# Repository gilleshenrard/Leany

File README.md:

<!--
SPDX-FileCopyrightText: 2025 Gilles Henrard <contact@gilleshenrard.com>

SPDX-License-Identifier: MIT
-->

# Leany - An open-Source Inclinometer

Leany is a fully open-source, production-ready inclinometer based on an ARM Cortex-M3 32-bits microcontroller.
It provides high-precision tilt measurements while adhering to strict embedded software and hardware design standards.

## About the Project
An inclinometer is a tool that measures how much something is tilted, specifically in two directions: pitch and roll.

- Pitch measures the tilt forward or backward. Imagine tilting your head down to look at your feet—that’s pitch.
- Roll measures the tilt side to side. It’s like tilting your head left or right to look over your shoulder—that’s roll.

So, if you're using an inclinometer, it can tell you exactly how much something is tilted forward, backward, or side to side. For example, if you're setting up equipment, you can use the inclinometer to make sure it’s positioned correctly, with no unwanted tilt in either direction. It’s useful in many situations, from construction to vehicles, ensuring that everything is set at the right angle for safety and precision.

Leany is designed for engineers, makers, and professionals who need a reliable, open, and customizable inclinometer. It offers precise tilt measurements and multiple operating modes while maintaining a strong focus on code quality, hardware reliability, and ease of integration.

### Key Features

- **Measurements**: Supports pitch and roll rotation axes with a precision of up to **0.1°**.
- **Hold Function**: Freezes screen updates to keep a measurement visible.
- **Slope Mode**: Measures angles relative to gravity (**absolute measurements**).
- **Angle Mode**: Measures angles relative to a user-defined zero position (**relative measurements**).

## Getting Started

Before contributing, please run the following :
```
git config --local include.path ../.gitconfig
```

To learn more about each part of the project, check the respective directories:

- **[Firmware (`firmware/`)](firmware/)** – Contains the firmware source code and instructions on how to build and flash it.
- **[PCB Design (`pcb/`)](pcb/)** – Contains the schematics and board design, along with instructions on generating production files.
- **[Documentation templates (`templates/`)](templates/)** – Contains example files to illustrate the structure documentation files should have.

## Contributions & Community

Leany is managed with the help of a **[Github Project](https://github.com/users/gilleshenrard/projects/3)**

Leany is fully open-source, and contributions are welcome! If you find a bug, have a suggestion, or want to improve the project, feel free to open an issue or submit a pull request.

Discussions are also encouraged—whether it's feature ideas, improvements, or troubleshooting. Join the community and help make Leany even better!

## License

This project is licensed under the **MIT License**, allowing for flexible use and modification.

---

Feel free to suggest any changes or enhancements to this README! 🚀

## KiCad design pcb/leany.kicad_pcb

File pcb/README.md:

<!--
SPDX-FileCopyrightText: 2026 Gilles Henrard <contact@gilleshenrard.com>

SPDX-License-Identifier: MIT
-->
# Leany Project PCB Documentation

Welcome to the Leany project's PCB documentation. This repository contains all the necessary files and information related to the PCB schematics and layouts for the Leany project.

## Table of Contents

- [Introduction](#introduction)
- [Getting Started](#getting-started)
- [Directory Structure](#directory-structure)
- [Contributing](#contributing)
- [License](#license)

## Introduction

This documentation provides an overview of the PCB schematics and layouts used in the Leany project. It includes detailed information on the design, components, and assembly instructions.

## Introduction

Inspect the project on [KiCanvas](https://kicanvas.org/?repo=https%3A%2F%2Fgithub.com%2Fgilleshenrard%2Fleany%2Ftree%2Fmain%2Fpcb)

## Generate the production files

1. Download KiCad from the [official website](https://kicad.org/).
2. Go to the pcb/ directory
3. Run the generation script located under resources/ :
    - *generate_production_files.bat* on Windows
    - *generate_production_files.sh* on Linux

## PCB fabrication

- Once the production files are generated, head to [JLCPCB](https://cart.jlcpcb.com/quote?orderType=1&stencilLayer=2&stencilWidth=100&stencilLength=100)

- Upload the zipped Gerber file, then, when the website is done processing it, choose the following non-default options :
  - Surface finish : LeadFree HASL
  - Enable PCB Assembly
- Then, click Next until arriving at the Bill Of Materials page.
- Upload the BOM and CPL files and click "Process BOM&CPL".
- Check that no error is shown on the components list page, and click Next.
- On the Components Placement page, move the components which are misplaced, then click Next.
- On the final page, click Save to Cart.

## Directory Structure
```
pcb/
└── resources
    ├── 3d-models
    ├── generate_production_files.sh
    └── generate_production_files.bat
```

### `3d-models`
This directory contains the additional 3D models needed to export the PCB as an STL file.
All the models are organised as [source]/[author]/[file]

### `resources`
Contains additional resources :
- `generate_production_files.sh` : A script to automatically generate and organise production files on Linux, with respect to JLCPCB standards.
- `generate_production_files.sh` : A script to automatically generate and organise production files on Windows, with respect to JLCPCB standards.

## CI/CD workflows
The PCB files are instected by a [Github Action](https://github.com/gilleshenrard/leany/actions/workflows/pcb_production_files.yml) upon push and pull request to run the **Electrical Rules Check** and **Design Rules Check** ensure the production files are easily generated.

## Gallery

## Contributing

Contributions to improve the PCB design and documentation are welcome. If you have any suggestions or improvements, please create a pull request or open an issue on the repository.

## License

The PCB files are licensed under CERN Open Hardware Licence Version 2 - Permissive. See the [CERN-OHL-P-2.0](https://github.com/gilleshenrard/leany/blob/27-fix-pcb-rev02-issues/LICENSES/CERN-OHL-P-2.0.txt) file for more details.

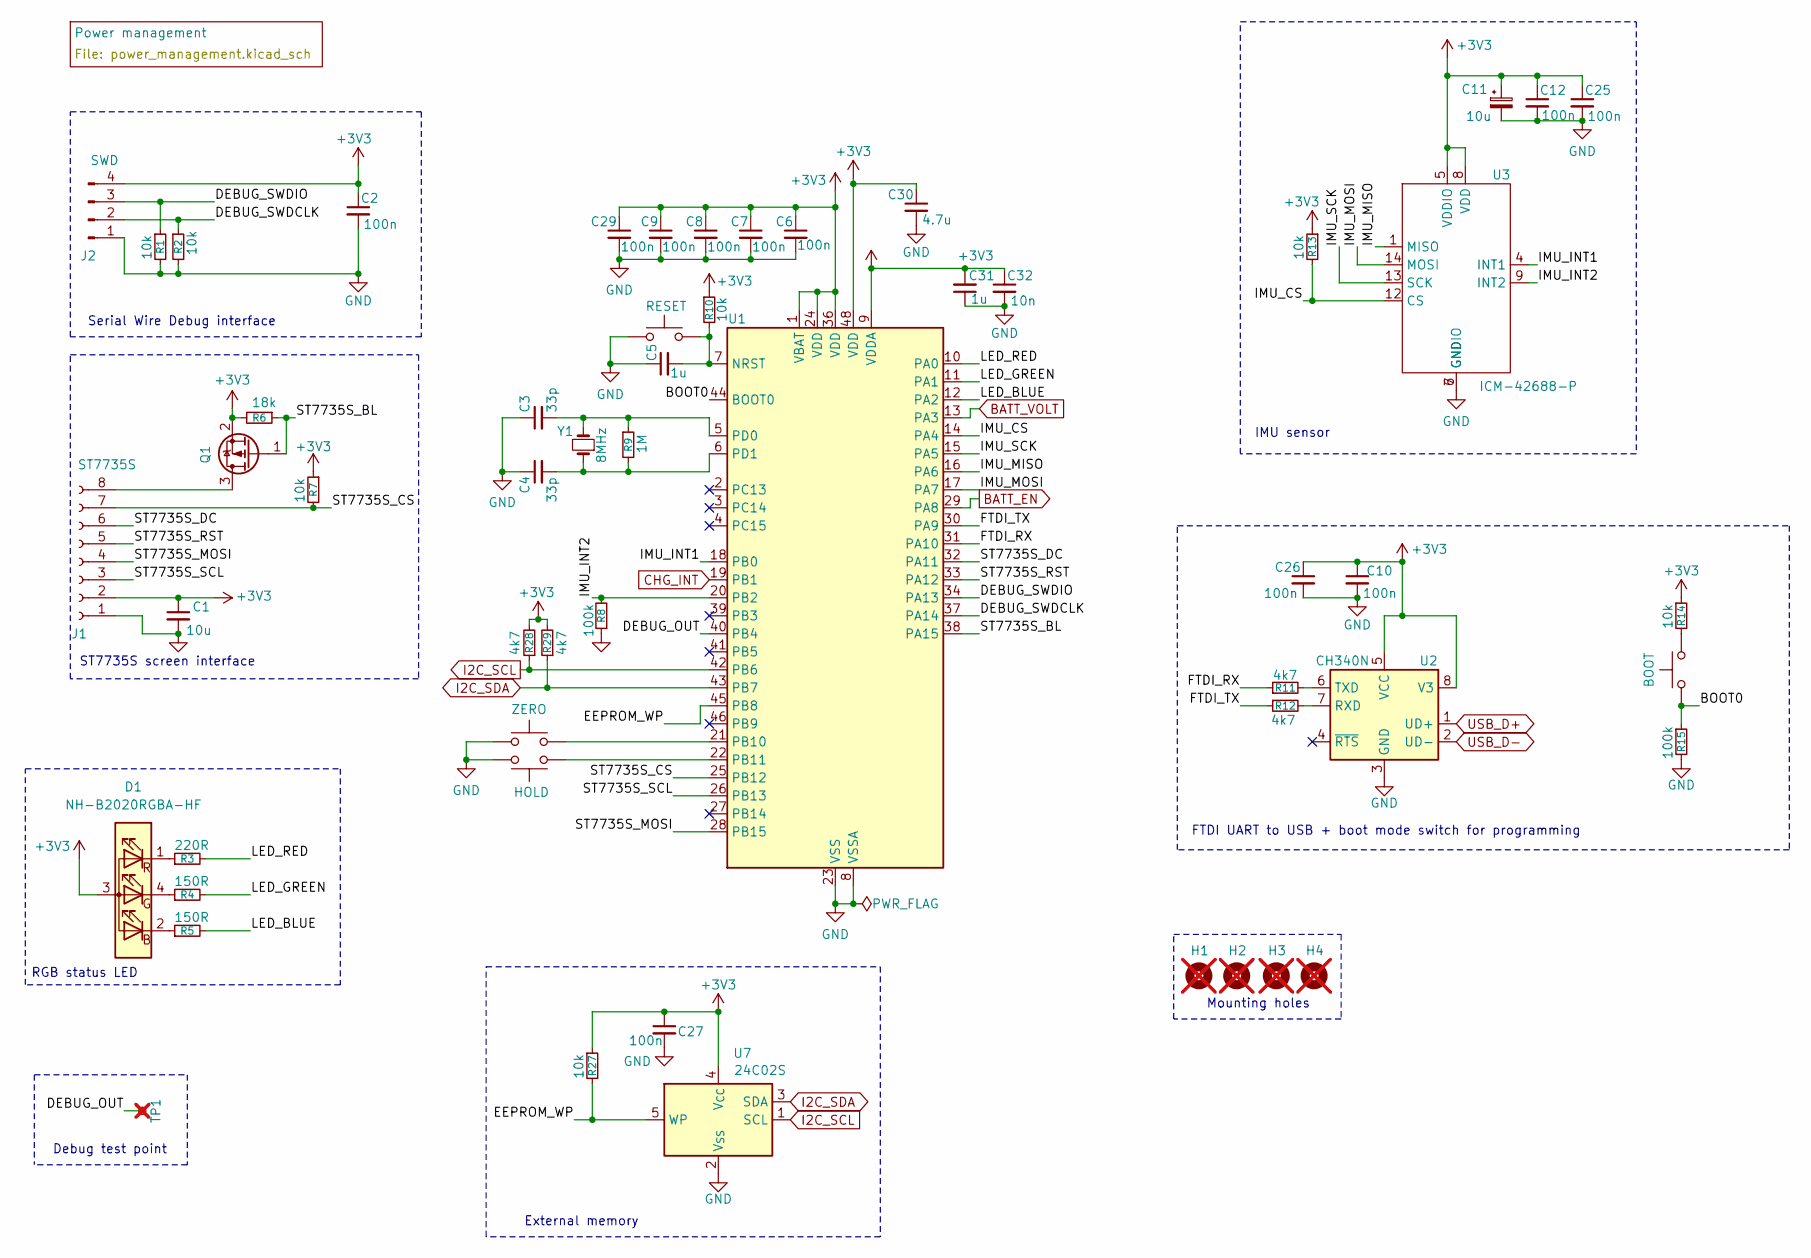
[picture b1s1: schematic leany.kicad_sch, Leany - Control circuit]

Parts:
C1, C11: 10u; C_0805_2012Metric; LCSC C15850
C2, C6, C7, C8, C9, C10, C12, C25, C26, C27, C29: 100n; C_0402_1005Metric; LCSC C1525
C3, C4: 33p; C_0402_1005Metric; LCSC C1562
C5, C31: 1u; C_0402_1005Metric; LCSC C52923
C30: 4.7u; C_0402_1005Metric; LCSC C23733
C32: 10n; C_0402_1005Metric; LCSC C15195
D1: NH-B2020RGBA-HF; LCSC C2874116
H1, H2, H3, H4: MountingHole; MountingHole_3.2mm_M3; not fitted
J1: ST7735S; LCSC C5224027
J2: SWD; PinHeader_1x04_P2.54mm_Horizontal; LCSC C2935929
Q1: AO3401A; SOT-23; LCSC C15127
R1, R2, R7, R10, R13, R14, R27: 10k; R_0402_1005Metric; LCSC C25744
R3: 220R; R_0402_1005Metric; LCSC C25091
R4, R5: 150R; R_0603_1608Metric; LCSC C22808
R6: 18k; R_0603_1608Metric; LCSC C25810
R8, R15: 100k; R_0402_1005Metric; LCSC C25741
R9: 1M; R_0402_1005Metric; LCSC C26083
R11, R12, R28, R29: 4k7; R_0402_1005Metric; LCSC C25900
SW1: ZERO; SW_Push_1P1T_NO_6x6mm_H9.5mm; LCSC C455120
SW2: HOLD; SW_Push_1P1T_NO_6x6mm_H9.5mm; LCSC C455120
SW3: RESET; SW_Push_1P1T_XKB_TS-1187A; LCSC C318884
SW4: BOOT; SW_Push_1P1T_XKB_TS-1187A; LCSC C318884
TP1: DEBUG_OUT; TestPoint_Pad_1.0x1.0mm; not fitted
U1: STM32F103C8Tx; LQFP-48_7x7mm_P0.5mm; LCSC C8734
U2: CH340N; SOP-8_3.9x4.9mm_P1.27mm; LCSC C2977777
U3: ICM-42688-P; LGA-14_3x2.5mm_P0.5mm_LayoutBorder3x4y; LCSC C784817
U7: 24C02S; SOT-23-5; LCSC C18723540
Y1: 8MHz; Crystal_SMD_Abracon_ABM3-2Pin_5.0x3.2mm; LCSC C115962

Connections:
+3V3: C1.1, C2.1, C6.1, C7.1, C8.1, C9.1, C10.1, C11.1, C12.1, C25.1, C26.1, C27.1, C29.1, C30.1, C31.2, C32.1, D1.3 (A), J1.2, J2.4, Q1.2 (S), R6.2, R7.1, R10.1, R13.1, R14.1, R27.1, R28.2, R29.2, U1.1 (VBAT), U1.9 (VDDA), U1.24 (VDD), U1.36 (VDD), U1.48 (VDD), U2.5 (VCC), U2.8 (V3), U3.5 (VDDIO), U3.8 (VDD), U7.4 (V_{CC}); also elsewhere on the board
/BOOT0: R15.1, SW4.2, U1.44 (BOOT0)
/DEBUG_OUT: TP1.1 (1_1), U1.40 (PB4)
/DEBUG_SWDCLK: J2.2, R2.1, U1.37 (PA14)
/DEBUG_SWDIO: J2.3, R1.1, U1.34 (PA13)
/EEPROM_WP: R27.2, U1.45 (PB8), U7.5 (WP)
/FTDI_RX: R11.1, U1.31 (PA10)
/FTDI_TX: R12.1, U1.30 (PA9)
/IMU_CS: R13.2, U1.14 (PA4), U3.12 (CS)
/IMU_INT1: U1.18 (PB0), U3.4 (INT1)
/IMU_INT2: R8.2, U1.20 (PB2), U3.9 (INT2)
/IMU_MISO: U1.16 (PA6), U3.1 (MISO)
/IMU_MOSI: U1.17 (PA7), U3.14 (MOSI)
/IMU_SCK: U1.15 (PA5), U3.13 (SCK)
/LED_BLUE: R5.2, U1.12 (PA2)
/LED_GREEN: R4.2, U1.11 (PA1)
/LED_RED: R3.2, U1.10 (PA0)
/ST7735S_BL: Q1.1 (G), R6.1, U1.38 (PA15)
/ST7735S_CS: J1.7, R7.2, U1.25 (PB12)
/ST7735S_DC: J1.6, U1.32 (PA11)
/ST7735S_MOSI: J1.4, U1.28 (PB15)
/ST7735S_RST: J1.5, U1.33 (PA12)
/ST7735S_SCL: J1.3, U1.26 (PB13)
BATT_EN: U1.29 (PA8); also elsewhere on the board
BATT_VOLT: U1.13 (PA3); also elsewhere on the board
CHG_INT: U1.19 (PB1); also elsewhere on the board
GND: C1.2, C2.2, C3.1, C4.1, C5.1, C6.2, C7.2, C8.2, C9.2, C10.2, C11.2, C12.2, C25.2, C26.2, C27.2, C29.2, C30.2, C31.1, C32.2, J1.1, J2.1, R1.2, R2.2, R8.1, R15.2, SW1.2, SW2.1, SW3.1, U1.8 (VSSA), U1.23 (VSS), U1.35 (VSS), U1.47 (VSS), U2.3 (GND), U3.6 (GNDIO), U3.7 (GND), U7.2 (V_{SS}); also elsewhere on the board
I2C_SCL: R28.1, U1.42 (PB6), U7.1 (SCL); also elsewhere on the board
I2C_SDA: R29.1, U1.43 (PB7), U7.3 (SDA); also elsewhere on the board
unnamed: D1.2 (BK), R5.1
unnamed: D1.4 (GK), R4.1
unnamed: D1.1 (RK), R3.1
unnamed: J1.8, Q1.3 (D)
unnamed: R14.2, SW4.1
unnamed: C5.2, R10.2, SW3.2, U1.7 (NRST)
unnamed: SW1.1, U1.21 (PB10)
unnamed: SW2.2, U1.22 (PB11)
unnamed: C3.2, R9.1, U1.5 (PD0), Y1.2
unnamed: C4.2, R9.2, U1.6 (PD1), Y1.1
unnamed: R12.2, U2.7 (RXD)
unnamed: R11.2, U2.6 (TXD)
USB_D+: U2.1 (UD+); also elsewhere on the board
USB_D-: U2.2 (UD-); also elsewhere on the board

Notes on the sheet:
FTDI UART to USB + boot mode switch for programming
Mounting holes
IMU sensor
Debug test point
ST7735S screen interface
RGB status LED
Serial Wire Debug interface
External memory

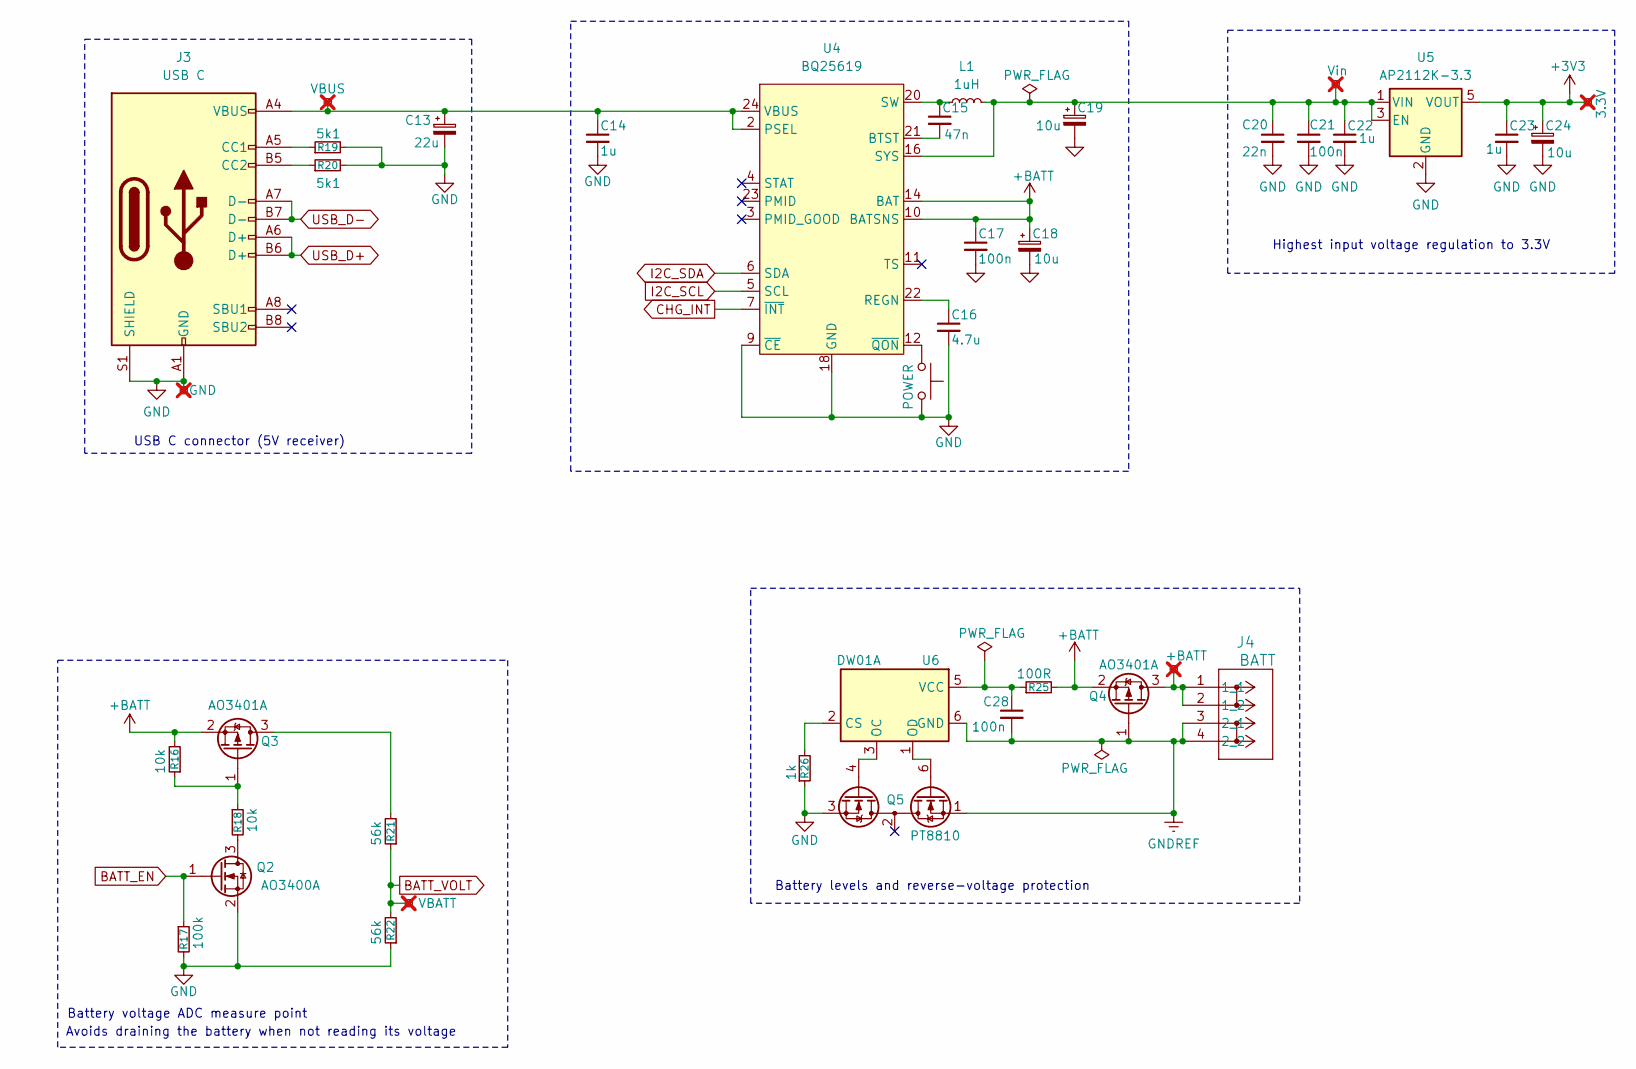
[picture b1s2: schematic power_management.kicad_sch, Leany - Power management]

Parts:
C13: 22u; C_0805_2012Metric; LCSC C45783
C14, C22, C23: 1u; C_0402_1005Metric; LCSC C52923
C15: 47n; C_0603_1608Metric; LCSC C1622
C16: 4.7u; C_0805_2012Metric; LCSC C1779
C17, C21, C28: 100n; C_0402_1005Metric; LCSC C1525
C18, C19, C24: 10u; C_0805_2012Metric; LCSC C15850
C20: 22n; C_0402_1005Metric; LCSC C1532
J3: USB C; USB_C_Receptacle_HRO_TYPE-C-31-M-12; LCSC C136423
J4: BATT; wago_2059-302_998-403; LCSC C2765060
L1: 1uH; L_1008_2520Metric; LCSC C98345
Q2: AO3400A; SOT-23; LCSC C20917
Q3, Q4: AO3401A; SOT-23; LCSC C15127
Q5: PT8810; SOT-23-6; LCSC C351413
R16, R18: 10k; R_0402_1005Metric; LCSC C25744
R17: 100k; R_0402_1005Metric; LCSC C25741
R19, R20: 5k1; R_0402_1005Metric; LCSC C25905
R21, R22: 56k; R_0603_1608Metric; LCSC C23206
R25: 100R; R_0402_1005Metric; LCSC C25076
R26: 1k; R_0402_1005Metric; LCSC C11702
SW5: POWER; SW_Tactile_SPST_Angled_PTS645Vx31-2LFS; LCSC C730034
TP2: GND; TestPoint_Pad_1.0x1.0mm; not fitted
TP3: VBUS; TestPoint_Pad_1.0x1.0mm; not fitted
TP4: VBATT; TestPoint_Pad_1.0x1.0mm; not fitted
TP5: +BATT; TestPoint_Pad_1.0x1.0mm; not fitted
TP6: Vin; TestPoint_Pad_1.0x1.0mm; not fitted
TP7: 3.3V; TestPoint_Pad_1.0x1.0mm; not fitted
U4: BQ25619; Texas_RGE0024H_VQFN-24-1EP_4x4mm_P0.5mm_EP2.7x2.7mm_Thermal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; LCSC C2864534
U5: AP2112K-3.3; SOT-23-5; LCSC C3021085
U6: DW01A; SOT-23-6; LCSC C2927799

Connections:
+3V3: C23.1, C24.1, TP7.1 (1_1), U5.5 (VOUT); also elsewhere on the board
+BATT: C17.1, C18.1, Q3.2 (S), Q4.2 (S), R16.2, R25.2, U4.10 (BATSNS), U4.13 (BAT), U4.14 (BAT)
BATT_EN: Q2.1 (G), R17.1; also elsewhere on the board
BATT_VOLT: R21.1, R22.2, TP4.1 (1_1); also elsewhere on the board
CHG_INT: U4.7 (~INT); also elsewhere on the board
GND: C13.2, C14.2, C16.2, C17.2, C18.2, C19.2, C20.2, C21.2, C22.2, C23.2, C24.2, J3.A1 (GND), J3.A12 (GND), J3.B1 (GND), J3.B12 (GND), J3.S1 (SHIELD), Q2.2 (S), Q5.3 (S2), R17.2, R19.2, R20.2, R22.1, R26.1, SW5.2, TP2.1 (1_1), U4.9 (~CE), U4.17 (GND), U4.18 (GND), U4.25 (GND), U5.2 (GND); also elsewhere on the board
GNDREF: C28.2, J4.3 (2_1), J4.4 (2_2), Q4.1 (G), Q5.1 (D1), U6.6 (GND)
I2C_SCL: U4.5 (SCL); also elsewhere on the board
I2C_SDA: U4.6 (SDA); also elsewhere on the board
unnamed: C15.1, L1.1, U4.19 (SW), U4.20 (SW)
unnamed: J3.A5 (CC1), R19.1
unnamed: J3.B5 (CC2), R20.1
unnamed: J4.1 (1_1), J4.2 (1_2), Q4.3 (D), TP5.1 (1_1)
unnamed: Q2.3 (D), R18.2
unnamed: Q3.3 (D), R21.2
unnamed: Q3.1 (G), R16.1, R18.1
unnamed: Q5.6 (G1), U6.1 (OD)
unnamed: Q5.4 (G2), U6.3 (OC)
unnamed: C15.2, U4.21 (BTST)
unnamed: C13.1, C14.1, J3.A4 (VBUS), J3.A9 (VBUS), J3.B4 (VBUS), J3.B9 (VBUS), TP3.1 (1_1), U4.1 (VAC), U4.2 (PSEL), U4.24 (VBUS)
unnamed: C16.1, U4.22 (REGN)
unnamed: SW5.1, U4.12 (~QON)
unnamed: R26.2, U6.2 (CS)
unnamed: C28.1, R25.1, U6.5 (VCC)
SYS: C19.1, C20.1, C21.1, C22.1, L1.2, TP6.1 (1_1), U4.15 (SYS), U4.16 (SYS), U5.1 (VIN), U5.3 (EN)
USB_D+: J3.A6 (D+), J3.B6 (D+); also elsewhere on the board
USB_D-: J3.A7 (D-), J3.B7 (D-); also elsewhere on the board

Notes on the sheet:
USB C connector (5V receiver)
Battery levels and reverse-voltage protection
Battery voltage ADC measure point
Highest input voltage regulation to 3.3V
Avoids draining the battery when not reading its voltage

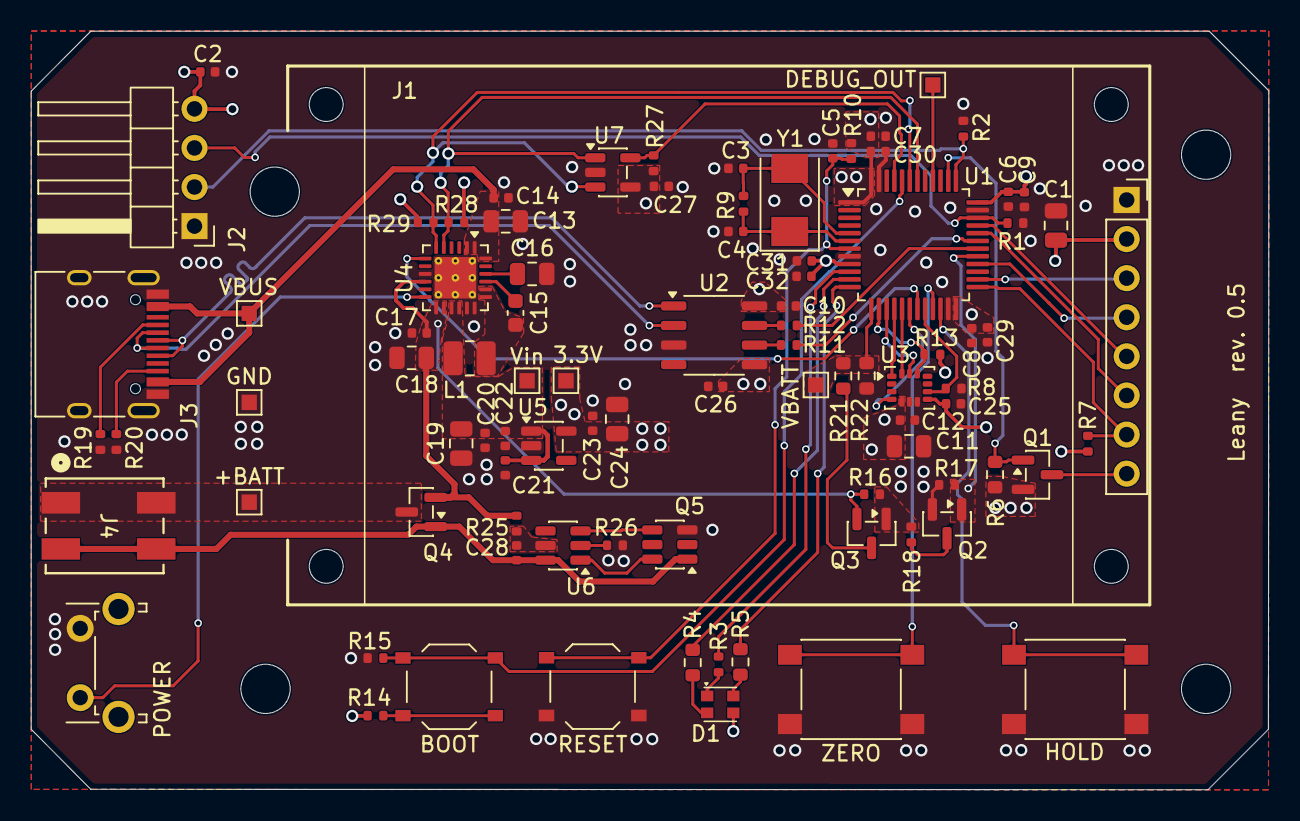
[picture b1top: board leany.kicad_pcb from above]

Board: 4 copper layers, 80.4 x 49.3 mm, 94 parts (0 on the bottom side), 61 nets.

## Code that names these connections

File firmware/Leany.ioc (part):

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Mcu.Name=STM32F103C(8-B)Tx
Mcu.Package=LQFP48
Mcu.UserName=STM32F103C8Tx
PA0-WKUP.GPIOParameters=GPIO_ModeDefaultPP,GPIO_Label
PA0-WKUP.GPIO_Label=LED_RED
PA0-WKUP.GPIO_ModeDefaultPP=GPIO_MODE_AF_OD
PA0-WKUP.Signal=S_TIM2_CH1_ETR
PA1.GPIOParameters=GPIO_ModeDefaultPP,GPIO_Label
PA1.GPIO_Label=LED_GREEN
PA1.GPIO_ModeDefaultPP=GPIO_MODE_AF_OD
PA1.Signal=S_TIM2_CH2
PA10.GPIOParameters=GPIO_Label
PA10.GPIO_Label=FTDI_RX
PA10.Mode=Asynchronous
PA10.Signal=USART1_RX
PA11.GPIOParameters=GPIO_Label
PA11.GPIO_Label=ST7735S_DC
PA11.Signal=GPIO_Output
PA12.GPIOParameters=PinState,GPIO_Label
PA12.GPIO_Label=ST7735S_RST
PA12.PinState=GPIO_PIN_SET
PA12.Signal=GPIO_Output
PA13.GPIOParameters=GPIO_Label
PA13.GPIO_Label=DEBUG_SWDIO
PA13.Mode=Serial_Wire
PA13.Signal=SYS_JTMS-SWDIO
PA14.GPIOParameters=GPIO_Label
PA14.GPIO_Label=DEBUG_SWCLK
PA14.Mode=Serial_Wire
PA14.Signal=SYS_JTCK-SWCLK
PA15.GPIOParameters=GPIO_Label
PA15.GPIO_Label=ST7735S_BL
PA15.Signal=GPIO_Output
PA2.GPIOParameters=GPIO_ModeDefaultPP,GPIO_Label
PA2.GPIO_Label=LED_BLUE
PA2.GPIO_ModeDefaultPP=GPIO_MODE_AF_OD
PA2.Signal=S_TIM2_CH3
PA3.GPIOParameters=GPIO_Label
PA3.GPIO_Label=BATT_VOLT
PA3.Signal=ADCx_IN3
PA4.GPIOParameters=GPIO_Speed,PinState,GPIO_PuPd,GPIO_Label
PA4.GPIO_Label=IMU_CS
PA4.GPIO_PuPd=GPIO_PULLUP
PA4.GPIO_Speed=GPIO_SPEED_FREQ_HIGH
PA4.PinState=GPIO_PIN_SET
PA4.Signal=GPIO_Output
PA5.GPIOParameters=GPIO_Label
PA5.GPIO_Label=IMU_SCL
PA5.Mode=Full_Duplex_Master
PA5.Signal=SPI1_SCK
PA6.GPIOParameters=GPIO_Label
PA6.GPIO_Label=IMU_MISO
PA6.Mode=Full_Duplex_Master
PA6.Signal=SPI1_MISO
PA7.GPIOParameters=GPIO_Label
PA7.GPIO_Label=IMU_MOSI
PA7.Mode=Full_Duplex_Master
PA7.Signal=SPI1_MOSI
PA8.GPIOParameters=GPIO_Label
PA8.GPIO_Label=BATT_EN
PA8.Signal=GPIO_Output
PA9.GPIOParameters=GPIO_Label
PA9.GPIO_Label=FTDI_TX
PA9.Mode=Asynchronous
PA9.Signal=USART1_TX
PB0.GPIOParameters=GPIO_PuPd,GPIO_Label
PB0.GPIO_Label=IMU_INT1
PB0.GPIO_PuPd=GPIO_PULLUP
PB0.Signal=GPXTI0
PB1.GPIOParameters=GPIO_PuPd,GPIO_Label
PB1.GPIO_Label=CHG_INT
PB1.GPIO_PuPd=GPIO_PULLDOWN
PB1.Signal=GPIO_Input
PB10.GPIOParameters=GPIO_PuPd,GPIO_Label
PB10.GPIO_Label=ZERO_BUTTON
PB10.GPIO_PuPd=GPIO_PULLUP
PB10.Signal=GPIO_Input
PB11.GPIOParameters=GPIO_PuPd,GPIO_Label
PB11.GPIO_Label=HOLD_BUTTON
PB11.GPIO_PuPd=GPIO_PULLUP
PB11.Signal=GPIO_Input
PB12.GPIOParameters=GPIO_Speed,PinState,GPIO_PuPd,GPIO_Label
PB12.GPIO_Label=ST7735S_CS
PB12.GPIO_PuPd=GPIO_PULLUP
PB12.GPIO_Speed=GPIO_SPEED_FREQ_HIGH
PB12.PinState=GPIO_PIN_SET
PB12.Signal=GPIO_Output
PB13.GPIOParameters=GPIO_Label
PB13.GPIO_Label=ST7735S_SCL
PB13.Mode=TX_Only_Simplex_Unidirect_Master
PB13.Signal=SPI2_SCK
PB15.GPIOParameters=GPIO_Label
PB15.GPIO_Label=ST7735S_MOSI
PB15.Mode=TX_Only_Simplex_Unidirect_Master
PB15.Signal=SPI2_MOSI
PB2.GPIOParameters=GPIO_PuPd,GPIO_Label
PB2.GPIO_Label=IMU_INT2
PB2.GPIO_PuPd=GPIO_PULLUP
PB2.Signal=GPXTI2
PB4.GPIOParameters=GPIO_Label
PB4.GPIO_Label=DEBUG_OUT
PB4.Signal=GPIO_Output
PB6.GPIOParameters=GPIO_Label
PB6.GPIO_Label=I2C_SCL
PB6.Mode=I2C
PB6.Signal=I2C1_SCL
PB7.GPIOParameters=GPIO_Label
PB7.GPIO_Label=I2C_SDA
PB7.Mode=I2C
PB7.Signal=I2C1_SDA
PB8.GPIOParameters=GPIO_PuPd,GPIO_Label,GPIO_ModeDefaultOutputPP
PB8.GPIO_Label=EEPROM_WP
PB8.GPIO_ModeDefaultOutputPP=GPIO_MODE_OUTPUT_OD
PB8.GPIO_PuPd=GPIO_NOPULL
PB8.Signal=GPIO_Output
PD0-OSC_IN.Mode=HSE-External-Oscillator
PD0-OSC_IN.Signal=RCC_OSC_IN
PD1-OSC_OUT.Mode=HSE-External-Oscillator
PD1-OSC_OUT.Signal=RCC_OSC_OUT
RCC.SYSCLKFreq_VALUE=72000000
RCC.SYSCLKSource=RCC_SYSCLKSOURCE_PLLCLK
board=custom

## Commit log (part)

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2026-05-05 refactor: make test code more readable (#53)
2026-05-05 refactor: Refactor GCC settings in gcc.cmake (#53)
2026-05-05 refactor: re-include the test suite into firmware cmake (#53)
2026-05-05 ci: make the the workflow use the test preset (#53)
2026-05-05 feat: add trivial unit tests (#53)
2026-05-05 refactor: reuse isContextReset() in bad samples count test (#53)
2026-05-05 fix: fix high rate test expectation (#53)
2026-05-05 feat: add unit tests (#53)
2026-05-05 refactor: make kMaxIntegralError public (#53)
2026-05-05 refactor: Refactor GCC warning flags in CMake file (#53)
2026-05-05 fix: start fixing new compile errors (#53)
2026-05-05 refactor: reformat test file (#53)
2026-05-05 ci: make clang-tidy step ignore more GCC flags (#53)
2026-05-05 refactor: enable cast-qual warnings (#53)
2026-05-05 ci: enable arith-conversion GCC warning (#53)
2026-05-05 ci: mirror firmware GCC warnings to unit tests (#53)
2026-05-05 chore: bump up actions versions (#53)
2026-05-06 fix: fix unit test failure (#53)
2026-05-06 feat: add ThrowTheSwitch/Unity v2.6.1 submodule to the project (#53)
2026-05-06 feat: implement vscode and github actions unit tests tasks (#53)
2026-05-06 feat: start implementing Unity test files (#53)
2026-05-06 fix: replace the LDO by an AP2112k-3.3 (#93)
2026-05-06 ﻿refactor: improve Github actions PCB workflow (#93)
2026-05-06 feat: reroute components (#93)
2026-05-06 chore: bump up kicad version to 10.0.0 (#93)
2026-05-06 chore: delete unused step files (#93)
2026-05-06 docs: update README and photos (#93)
2026-05-06 fix: update ST7735S 3d model (#93)
2026-05-06 refactor: update symbols and footprints libraries (#93)
2026-05-06 docs: untrack local *.kicad_prl files (#93)
2026-05-06 chore: update schematics and pcb to Kicad 10.0.0.0 (#93)
2026-05-06 chore: update kicad 10 symbols and footprints (#93)
2026-05-06 ci: Add issue templates to REUSE.toml (#93)
    Updated copyright year from 2025 to 2026 in annotations.
2026-05-06 ﻿feat: track FreeCAD files into Git LFS (#45)
2026-05-06 ﻿feat: start designing the test angled bracket and slide-in support (#45)
2026-05-06 feat: start reimplementing mount plate (#45)
2026-05-06 feat: replace stl files creation by step files (#45)
2026-05-06 feat: add features to the mounting plate (#45)
2026-05-06 feature: adapt jig design to the new pcb (#45)
2026-05-06 style: move validation script file and rename CAD/ to cad/ (#45)
2026-05-06 ci: fix paths in workflow (#45)
2026-05-06 refactor : fix kicad_pcb files rules in gitattributes (#45)
2026-05-06 ci: update actions/checkout version (#45)
2026-05-06 ci: add a debug step in workflow (#45)
2026-05-06 ci: try flushing stdin before rerunning the loop (#45)
2026-06-30 refactor: fallback to rev 0.3 and update files (#98)
2026-06-30 ci: fix workflow configuration (#98)
2026-06-30 fix: remove test points from BOM and CPL (#98)
2026-06-30 fix: re-configure project so it fits rev 0.3 (#98)
2026-06-30 ﻿feat: replace stl files creation by step files (#45)

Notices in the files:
pcb/leany.kicad_pcb:
Copyright (c) 2023 Gilles Henrard
pcb/leany.kicad_sch:
Copyright (c) 2026 Gilles Henrard
